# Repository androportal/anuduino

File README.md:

low-cost-arduino
================

A two dollar arduino compatible board based on ATtiny-85 chip

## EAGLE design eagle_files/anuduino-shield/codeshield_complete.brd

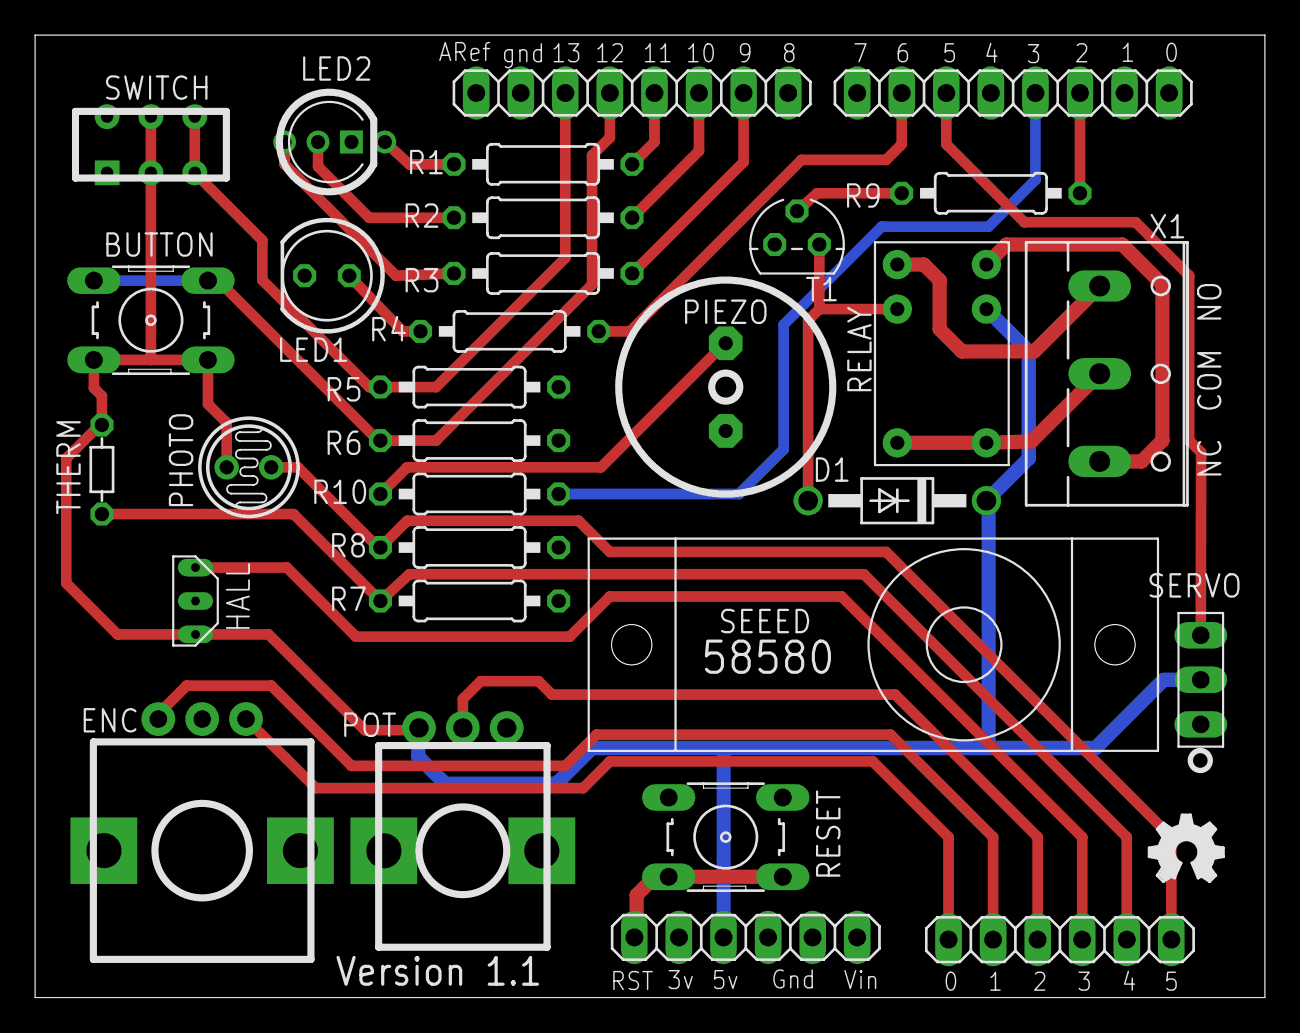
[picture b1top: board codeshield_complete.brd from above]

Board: 2 copper layers, 70.1 x 54.9 mm, 31 parts (0 on the bottom side), 28 nets.

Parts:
BUTTON: B3F-10XX
D1: 1N4004; DO41-10
ENC: EVE_ROTARY_ENCODER; 12MM_ENCODER
HALL: SS49E; TO_92_SHORT
JP1, JP2: 1X08
JP3, JP4: 1X06
LED1: LED5MM
LED2: RGB LED; RGB_VERTICAL
PHOTO: CdS Photocell; TO46-VT200
PIEZO: PS1240P02BT
POT: EVU_POTENTIOMETER; VERT_POT
R1, R2, R3, R4, R5, R6, R7, R8, R9, R10: 0207/10
RELAY: TSC_1FORMC; TSC_RELAY
RESET: B3F-10XX
SERVO: SG90_SERVO
SWITCH: MHSS_MICROSLIDE; SLIDE_SWITCH
T1: 2N3904; TO92
THERM: Thermistor; R-5
U$1: OSHW_FILLX150_NOTEXT
X1: W237-103

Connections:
+5V: BUTTON.3, BUTTON.4, D1.C, HALL.V+, JP3.4, PHOTO.1, POT.3, RELAY.2, SERVO.2, SWITCH.3, SWITCH.4, THERM.1
BLUE: JP1.3, R2.2
BUTTON: BUTTON.1, BUTTON.2, JP1.5, R6.2
GND: ENC.COM, HALL.V-, JP1.7, JP3.2, JP3.3, LED1.K, LED2.2, PIEZO.2, POT.1, R5.1, R6.1, R7.2, R8.2, RESET.1, RESET.2, SERVO.1, T1.3
GREEN: JP1.2, R3.2
HALL_SENSOR: HALL.OUT, JP4.3
LED: JP2.7, R4.2
unnamed: LED2.1, R1.1
unnamed: LED2.3, R2.1
unnamed: LED2.4, R3.1
unnamed: PIEZO.1, R10.1
unnamed: D1.A, RELAY.5, T1.1
unnamed: LED1.A, R4.1
unnamed: RELAY.1, X1.3
unnamed: RELAY.3, RELAY.4, X1.2
unnamed: RELAY.6, X1.1
unnamed: R9.2, T1.2
PHOTOCELL: JP4.1, PHOTO.2, R8.1
PIEZO: JP2.4, R10.2
POTENTIOMETER: JP4.4, POT.2
RED: JP1.4, R1.2
RELAY: JP2.3, R9.1
RESET: JP3.6, RESET.3, RESET.4
ROTARY_A: ENC.A, JP4.6
ROTARY_B: ENC.B, JP4.5
SERVO: JP2.6, SERVO.3
SWITCH: JP1.6, R5.2, SWITCH.5, SWITCH.6
THERMISTOR: JP4.2, R7.1, THERM.2

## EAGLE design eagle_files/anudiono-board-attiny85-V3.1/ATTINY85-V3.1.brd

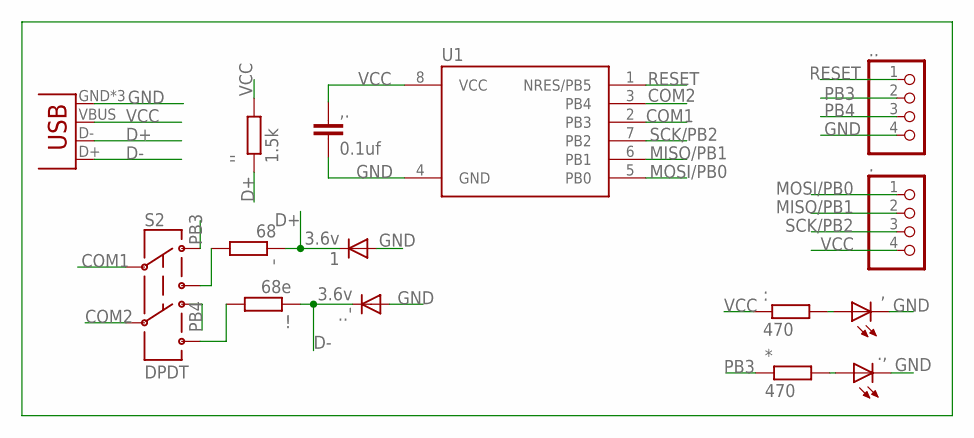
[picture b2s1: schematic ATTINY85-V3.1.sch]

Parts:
1, ..': 3.6v; MINIMELF
!: 68e; M0805
': 68; M0805
'': 1.5k; M0805
*: 470; M0805
+: USB-MICROB
,: LEDSML0805; SML0805
,.: 0.1uf; C0805K
., ..: HEADER-1X4ROUND; 1X04_ROUND
.,: LEDSML0805; SML0805
:: 470; M0805
S2: DPDT; AYZ0202
U1: ATTINY85-20S; SOIC8_EIAJ_208MIL

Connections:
COM1: S2.2, U1.2 (PB3)
COM2: S2.5, U1.3 (PB4)
D+: 1.C, '.1, ''.1, +.D-
D-: !.1, +.D+, ..'.C
GND: 1.A, +.GND, +.MT1 (GND), +.MT2 (GND), ,.C, ,..2, .,.C, ...4, ..'.A, U1.4 (GND)
MISO/PB1: ..2, U1.6 (PB1)
MOSI/PB0: ..1, U1.5 (PB0)
unnamed: ,.A, :.2
unnamed: '.2, S2.3
unnamed: !.2, S2.6
unnamed: *.2, .,.A
PB3: *.1, ...2, S2.1
PB4: ...3, S2.4
RESET: ...1, U1.1 (NRES/PB5)
SCK/PB2: ..3, U1.7 (PB2)
VCC: ''.2, +.VBUS, ,..1, ..4, :.1, U1.8 (VCC)

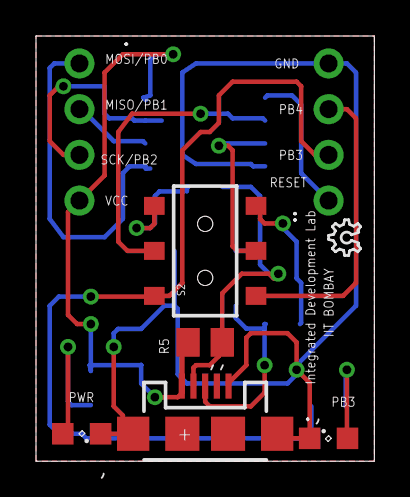
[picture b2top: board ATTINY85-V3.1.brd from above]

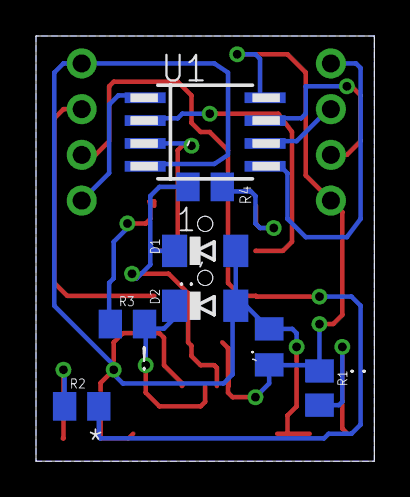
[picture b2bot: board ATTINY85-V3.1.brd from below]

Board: 2 copper layers, 18.8 x 23.6 mm, 16 parts (8 on the bottom side), 16 nets.

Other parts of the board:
U$1: OSHW_6X70_NOTEXT

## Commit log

2013-09-04 added documentation of anuduino
2013-09-04 added missing image files
2013-09-05 modified errors
2013-09-05 added missing image for example lm35
2013-09-09 fixed few typos and resize image sizes for sphinx
2013-09-09 renamed getting_started_sphinx.rst to getting_started.rst
2013-09-09 fixed number issue in pdf and html
2013-09-14 commented 6k explanation
2013-09-19 fixed typo
2013-10-01 run.sh will read data and use gnuplot-X11 to plot automatically
2014-02-27 fixed an wrong connection in temperaturesensor image
2014-03-06 removed solder.png as one of the diode was misplaced
2014-04-23 added email
2014-11-13 added eagle files

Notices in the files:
parts and their libraries:
SparkFun-Connectors: Licensing: Creative Commons ShareAlike 4.0 International - https://creativecommons.org/licenses/by-sa/4.0
microbuilder: This work is placed in the public domain, and may be freely used for commercial and non-commercial work with the following conditions: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
